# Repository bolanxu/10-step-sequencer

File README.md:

# Pocket 10-Step Electronic Sequencer

This is a simple sequencer project based on one CD4017 and three 555 timers. In 4th grade, I was learning about the 4017 and 555 timers and I had the inspiration to create a form of musical instrument by combining them togther. My first prototype was made on a breadboard and I remember that it was the most complicated circuit I had made up until that point in time. A few years later in 2021, I was learning how to use Eagle PCB and decided to make this circuit into a PCB. And the Pocket Sequencer was born!

## Circuit

The schematic is fairly straightforward. The first 555 timer (U2) is running in astable mode and is used to drive the 4017 with a clock pulse. The 4017, which is a decade counter activates each output and moves on to the next with each clock pulse.
The pot R2 controls the speed of the counter which controls how fast each step in the sequencer is.
Each output of the 4017 is then connected to a pot (R5 - R14) which controls each individual tone in the sequencer by changing the astable operation of U2 which is the second 555 timer. By varying the value of each of the pots and the value of R3, the freqency of the timer is varied, changing the tone at the output.
The output of U3 is then connected to the trigger pin of U4. The third 555 timer is running in monostable mode which means that each pulse on the trigger pin creates a pulse on the output pin for a set length of time controlled by the value of R4.
In addition to the tones, the row of led's will light up at each corresponding step in the sequence.
The values of R3 and R4 can change the overall tone of the sequencer and when adjusted in conjuction with each other some very interesting tones can be created!
The recommended power source is a 9V battery, but anything 5V to 16V should work fine.

Connect a battery and a speaker to the pin connectors and have fun playing with the trimmers and make some music!

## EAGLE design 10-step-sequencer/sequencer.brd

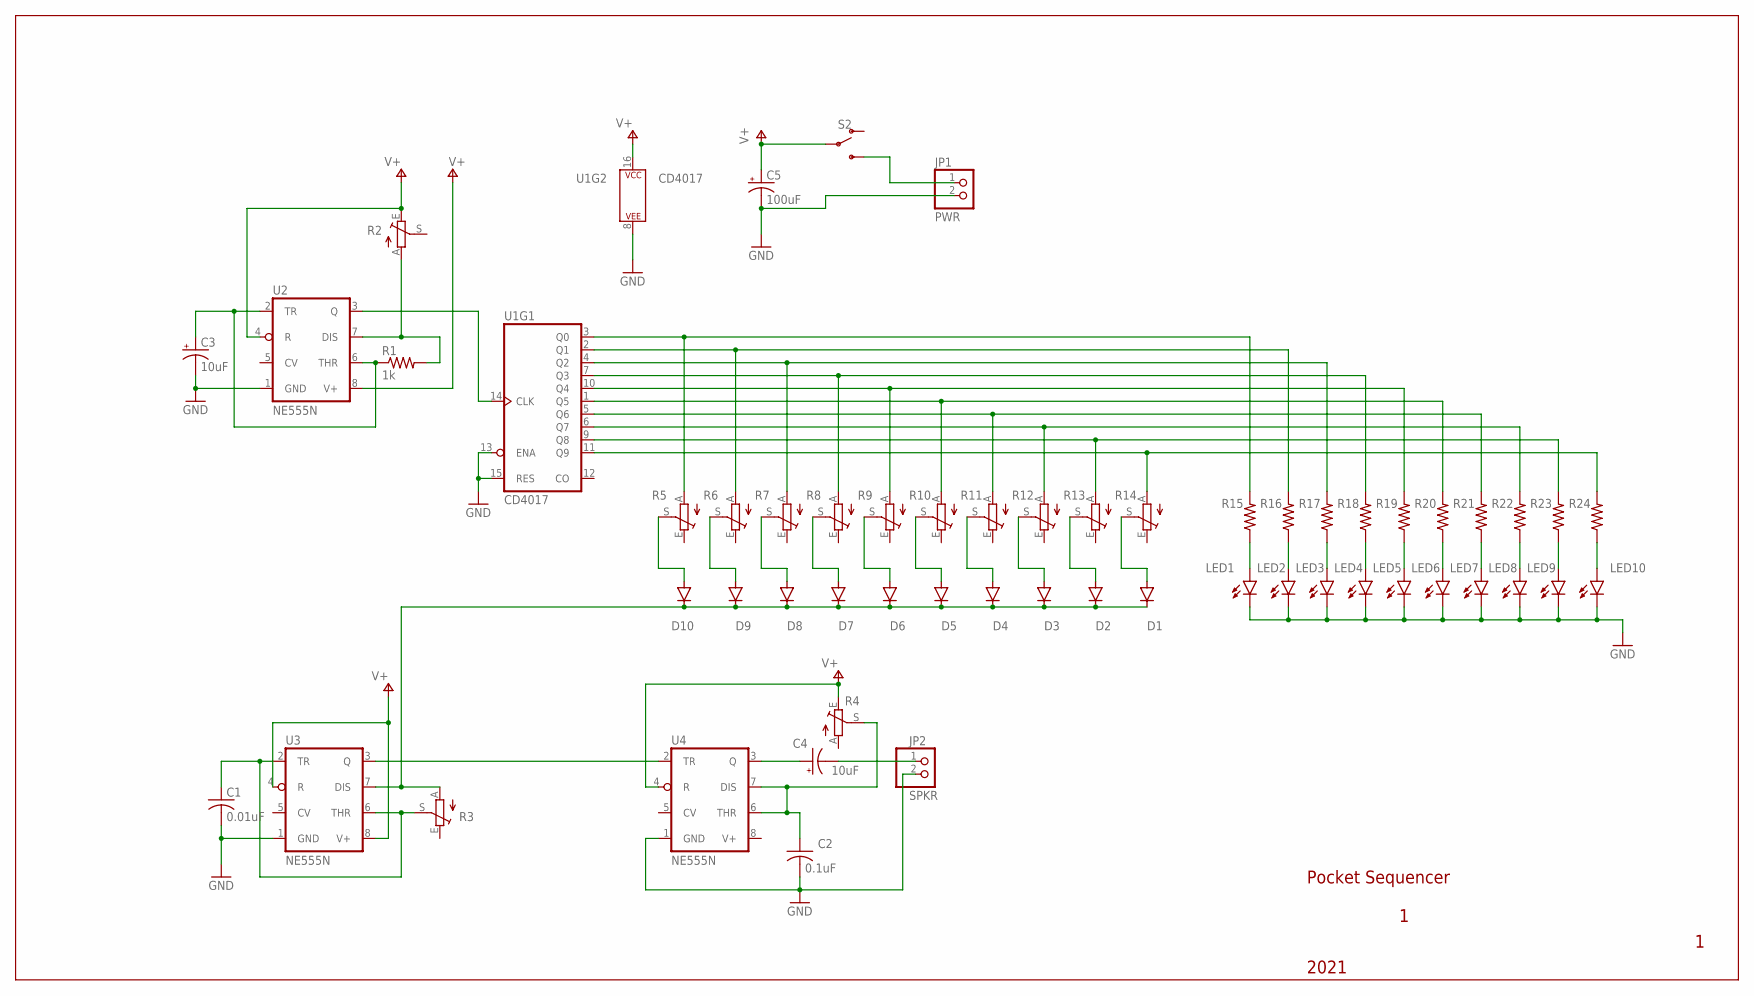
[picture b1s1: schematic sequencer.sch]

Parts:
C1: 0.01uF; C025-025X050
C2: 0.1uF; C025-025X050
C3, C4: 10uF; E2,5-6
C5: 100uF; E2,5-7
D1, D2, D3, D4, D5, D6, D7, D8, D9, D10: 1N4148DO35-7; DO35-7
JP1: PWR; 1X02
JP2: SPKR; 1X02
LED1, LED2, LED3, LED4, LED5, LED6, LED7, LED8, LED9, LED10: LED3MM
R1: 1k; 0207/7
R2, R3, R4, R5, R6, R7, R8, R9, R10, R11, R12, R13, R14: TRIM_EU-CT6; CT6
R15, R16, R17, R18, R19, R20, R21, R22, R23, R24: R-US_0207/7; 0207/7
S2: SWITCH-SPDT-PTH-8.6X4.3MM; SWITCH_SPDT_8.6X4.3MM
U1: CD4017; DIP16
U2, U3, U4: NE555N; DIL08

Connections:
GND: C1.2, C2.2, C3.-, C5.-, JP1.2, JP2.2, LED1.K (C), LED2.K (C), LED3.K (C), LED4.K (C), LED5.K (C), LED6.K (C), LED7.K (C), LED8.K (C), LED9.K (C), LED10.K (C), U1.8 (P$V-), U1.13 (ENA), U1.15 (RES), U2.1 (GND), U3.1 (GND), U4.1 (GND)
unnamed: R1.2, R2.A, U2.7 (DIS)
unnamed: C3.+, R1.1, U2.2 (TR), U2.6 (THR)
unnamed: U1.14 (CLK), U2.3 (Q)
unnamed: R5.A, R15.2, U1.3 (Q0)
unnamed: R6.A, R16.2, U1.2 (Q1)
unnamed: R7.A, R17.2, U1.4 (Q2)
unnamed: R8.A, R18.2, U1.7 (Q3)
unnamed: R9.A, R19.2, U1.10 (Q4)
unnamed: R10.A, R20.2, U1.1 (Q5)
unnamed: R11.A, R21.2, U1.5 (Q6)
unnamed: R12.A, R22.2, U1.6 (Q7)
unnamed: R13.A, R23.2, U1.9 (Q8)
unnamed: R14.A, R24.2, U1.11 (Q9)
unnamed: D10.A, R5.S
unnamed: D9.A, R6.S
unnamed: D8.A, R7.S
unnamed: D7.A, R8.S
unnamed: D6.A, R9.S
unnamed: D5.A, R10.S
unnamed: D4.A, R11.S
unnamed: D3.A, R12.S
unnamed: D2.A, R13.S
unnamed: D1.A, R14.S
unnamed: LED1.A, R15.1
unnamed: LED2.A, R16.1
unnamed: LED3.A, R17.1
unnamed: LED4.A, R18.1
unnamed: LED5.A, R19.1
unnamed: LED6.A, R20.1
unnamed: LED7.A, R21.1
unnamed: LED8.A, R22.1
unnamed: LED9.A, R23.1
unnamed: LED10.A, R24.1
unnamed: C2.1, R4.S, U4.6 (THR), U4.7 (DIS)
unnamed: JP1.1, S2.3 (S)
unnamed: C1.1, R3.S, U3.2 (TR), U3.6 (THR)
unnamed: U3.3 (Q), U4.2 (TR)
unnamed: D1.C, D2.C, D3.C, D4.C, D5.C, D6.C, D7.C, D8.C, D9.C, D10.C, R3.A, U3.7 (DIS)
unnamed: C4.+, U4.3 (Q)
unnamed: C4.-, JP2.1
V+: C5.+, R2.E, R4.E, S2.2, U1.16 (P$V+), U2.4 (R), U2.8 (V+), U3.4 (R), U3.8 (V+), U4.4 (R), U4.8 (V+)

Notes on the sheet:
Pocket Sequencer
2021

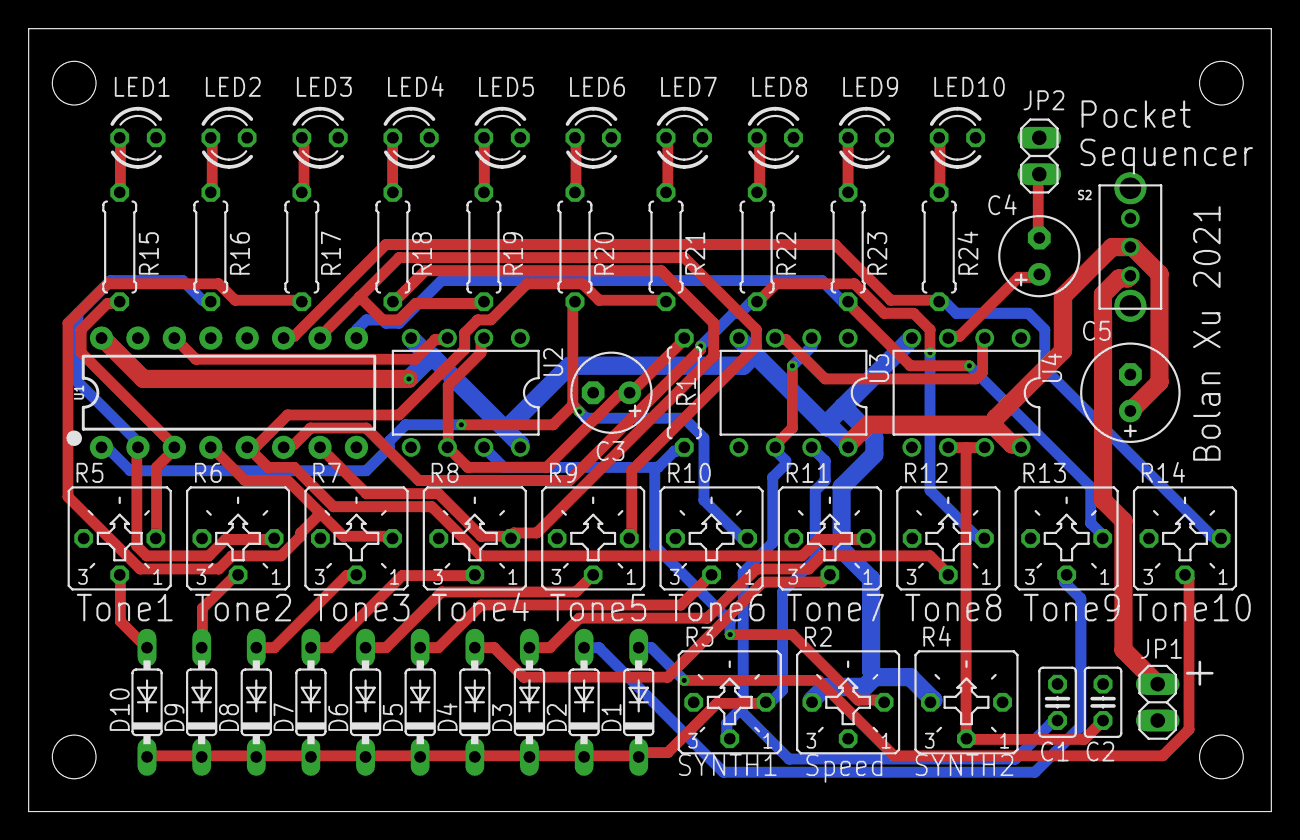
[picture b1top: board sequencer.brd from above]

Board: 2 copper layers, 86.7 x 54.6 mm, 56 parts (0 on the bottom side), 42 nets.

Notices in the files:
parts and their libraries:
SparkFun-IC-Logic: Licensing: Creative Commons ShareAlike 4.0 International - https://creativecommons.org/licenses/by-sa/4.0
